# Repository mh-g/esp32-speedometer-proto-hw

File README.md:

# esp32-speedometer-proto-hw
prototype hardware for ESP32 speedometer project

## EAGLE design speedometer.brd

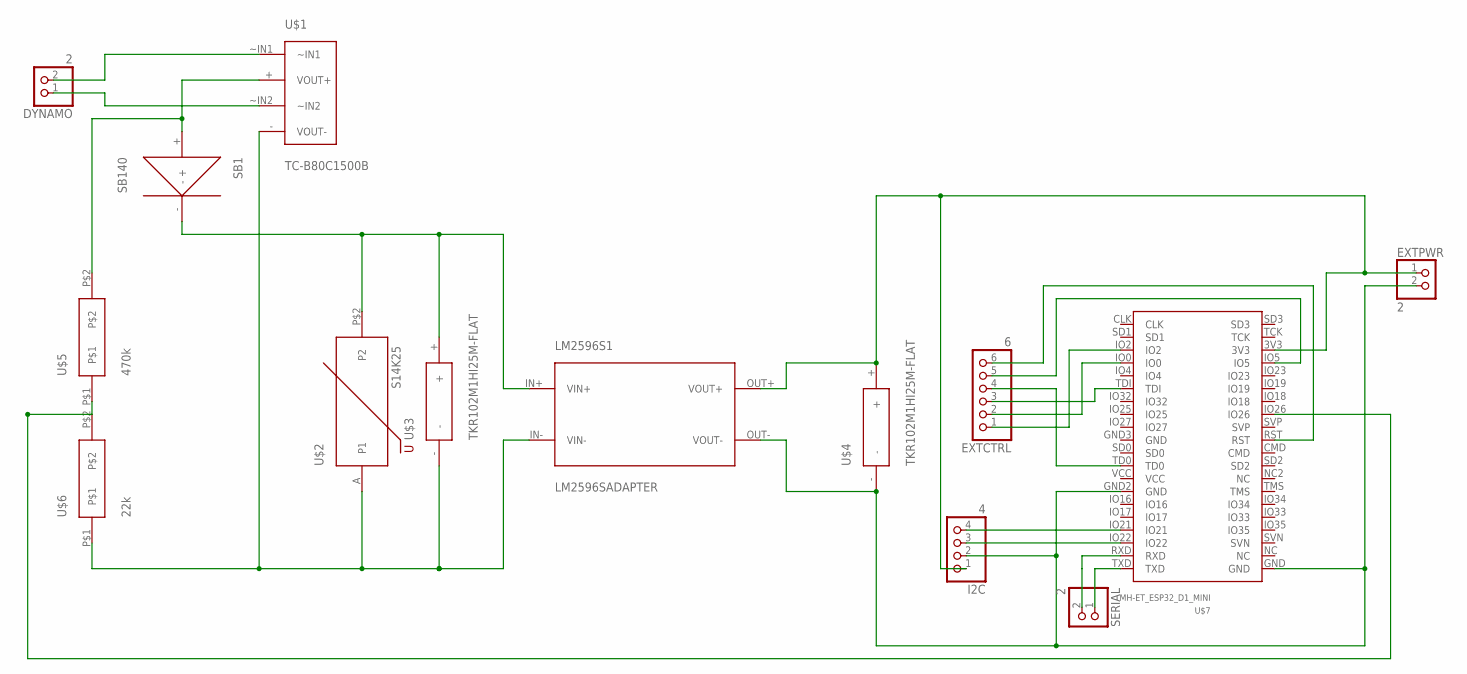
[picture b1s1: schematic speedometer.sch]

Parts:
DYNAMO: 2; 1X02
EXTCTRL: 6; 1X06
EXTPWR: 2; 1X02
I2C: 4; 1X04
LM2596S1: LM2596SADAPTER
SB1: SB140
SERIAL: 2; 1X02
U$1: TC-B80C1500B
U$2: S14K25
U$3, U$4: TKR102M1HI25M-FLAT
U$5: 470k; RESISTOR
U$6: 22k; RESISTOR
U$7: MH-ET_ESP32_D1_MINI

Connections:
unnamed: DYNAMO.2, U$1.~IN1
unnamed: DYNAMO.1, U$1.~IN2
unnamed: SB1.+, U$1.+ (VOUT+), U$5.P$2
unnamed: LM2596S1.IN+ (VIN+), SB1.-, U$2.P$2 (P2), U$3.+
unnamed: LM2596S1.IN- (VIN-), U$1.- (VOUT-), U$2.A (P1), U$3.-, U$6.P$1
unnamed: EXTPWR.2, I2C.2, LM2596S1.OUT- (VOUT-), U$4.-, U$7.GND, U$7.GND2 (GND)
unnamed: EXTPWR.1, I2C.1, LM2596S1.OUT+ (VOUT+), U$4.+, U$7.3V3
unnamed: U$5.P$1, U$6.P$2, U$7.IO26
unnamed: SERIAL.2, U$7.RXD
unnamed: SERIAL.1, U$7.TXD
unnamed: I2C.4, U$7.IO21
unnamed: I2C.3, U$7.IO22
unnamed: EXTCTRL.1, U$7.IO2
unnamed: EXTCTRL.2, U$7.IO0
unnamed: EXTCTRL.3, U$7.TDI
unnamed: EXTCTRL.4, U$7.TD0
unnamed: EXTCTRL.5, U$7.IO5
unnamed: EXTCTRL.6, U$7.RST

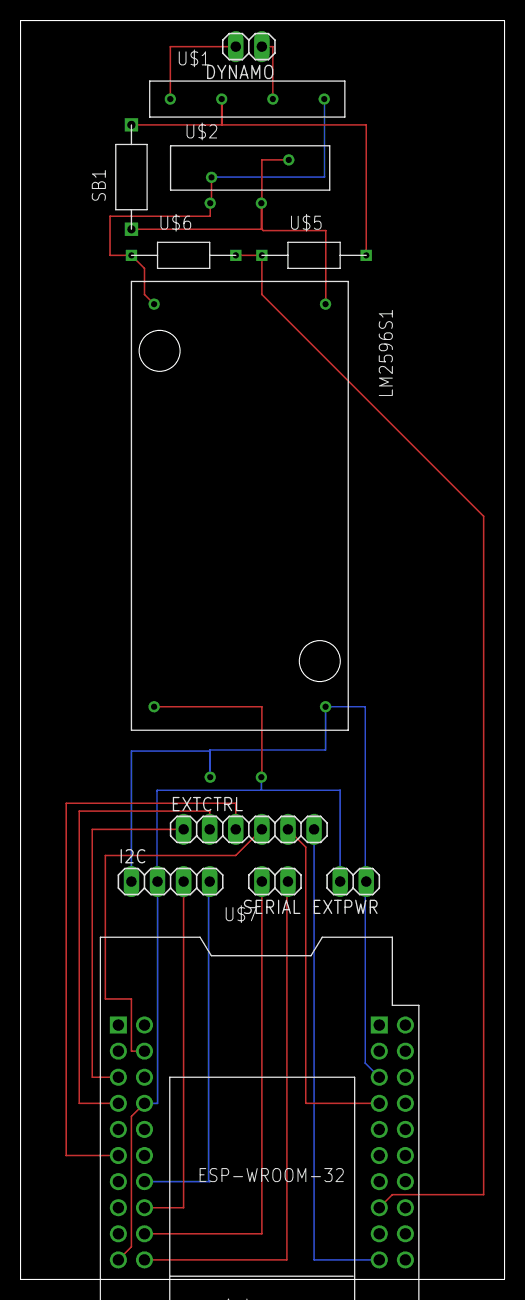
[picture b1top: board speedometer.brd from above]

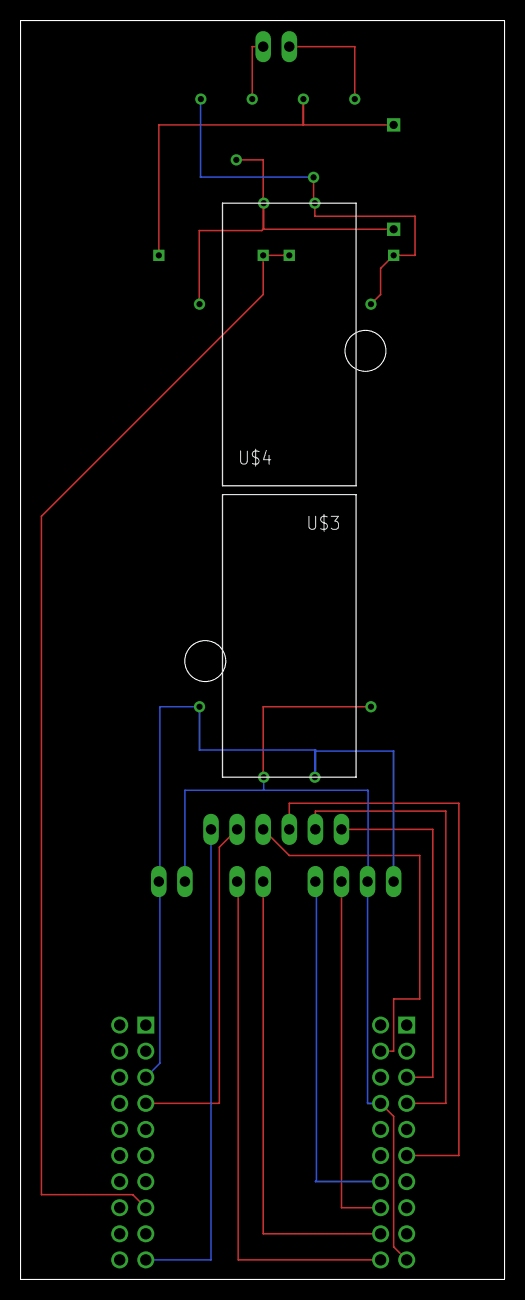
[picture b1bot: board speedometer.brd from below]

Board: 4 copper layers, 47.1 x 122.6 mm, 14 parts (2 on the bottom side), 18 nets.

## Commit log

2023-01-11 Initial upload
